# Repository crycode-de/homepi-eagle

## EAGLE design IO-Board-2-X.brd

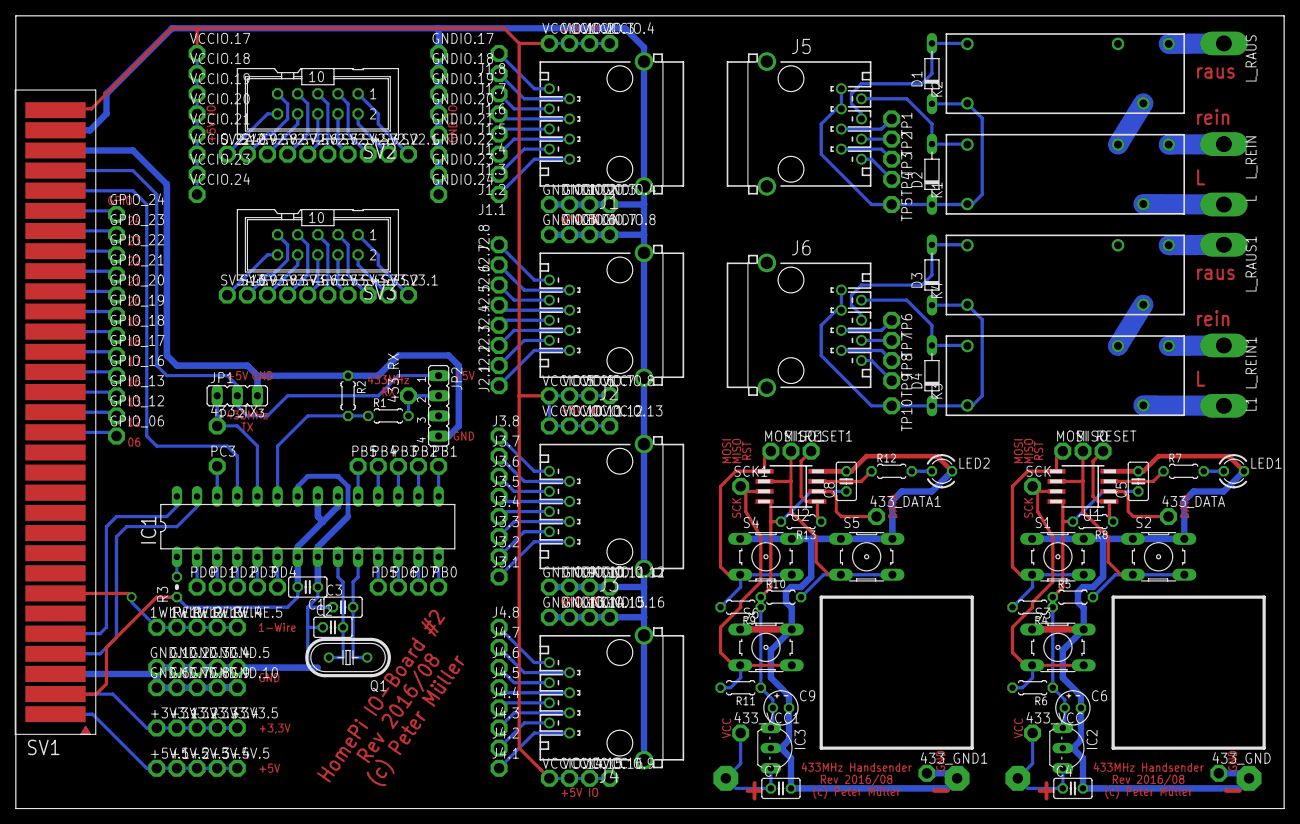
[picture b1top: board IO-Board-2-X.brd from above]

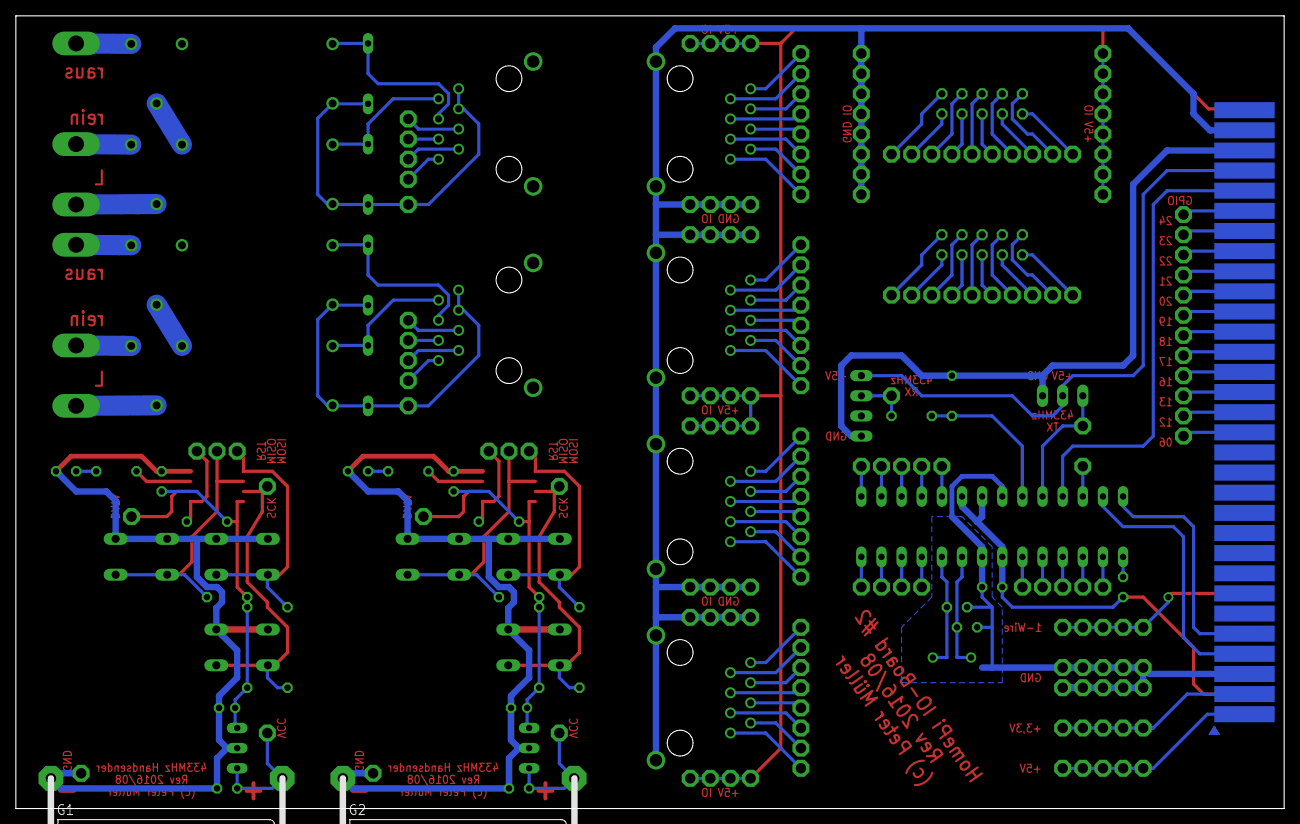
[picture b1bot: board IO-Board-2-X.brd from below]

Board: 2 copper layers, 160.0 x 100.0 mm, 241 parts (2 on the bottom side), 138 nets.

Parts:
1WIRE.1, 1WIRE.2, 1WIRE.3, 1WIRE.4, 1WIRE.5, 433_DATA, 433_DATA1, 433_GND, 433_GND1, 433_RX, 433_TX, 433_VCC, 433_VCC1: TPPAD1-13; P1-13
+3V3.1, +3V3.2, +3V3.3, +3V3.4, +3V3.5, +5V.1, +5V.2, +5V.3, +5V.4, +5V.5: TPPAD1-13; P1-13
C1, C4, C5, C7, C8: 100nF; C025-025X050
C2, C3: 22pF; C025-025X050
C6, C9: 10µF; E2-4
D1, D2, D3, D4: D-7.5
G1, G2: GP23A
GND.1, GND.2, GND.3, GND.4, GND.5, GND.6, GND.7, GND.8, GND.9, GND.10: TPPAD1-13; P1-13
GNDIO.1, GNDIO.2, GNDIO.3, GNDIO.4, GNDIO.5, GNDIO.6, GNDIO.7, GNDIO.8, GNDIO.9, GNDIO.10, GNDIO.11, GNDIO.12, GNDIO.13, GNDIO.14, GNDIO.15, GNDIO.16, GNDIO.17, GNDIO.18, GNDIO.19, GNDIO.20, GNDIO.21, GNDIO.22, GNDIO.23, GNDIO.24: TPPAD1-13; P1-13
GPIO_06, GPIO_12, GPIO_13, GPIO_16, GPIO_17, GPIO_18, GPIO_19, GPIO_20, GPIO_21, GPIO_22, GPIO_23, GPIO_24: TPPAD1-13; P1-13
IC1: MEGA8-P; DIL28-3
IC2, IC3: LM2936-5.0; TO92-INLINE
J1, J2, J3, J4, J5, J6: 555153-1
J1.1, J1.2, J1.3, J1.4, J1.5, J1.6, J1.7, J1.8, J2.1, J2.2, J2.3, J2.4, J2.5, J2.6, J2.7, J2.8, J3.1, J3.2, J3.3, J3.4, J3.5, J3.6, J3.7, J3.8, J4.1, J4.2, J4.3, J4.4, J4.5, J4.6, J4.7, J4.8: TPPAD1-13; P1-13
JP1: JP2
JP2: JP4
K1, K2, K3, K4: FINDER-43.41
L, L1: TPPAD1-20Y; P1-20Y
LED1, LED2: LED3MM
L_RAUS, L_RAUS1: TPPAD1-20Y; P1-20Y
L_REIN, L_REIN1: TPPAD1-20Y; P1-20Y
MISO, MISO1: TPPAD1-13; P1-13
MOSI, MOSI1: TPPAD1-13; P1-13
PB0, PB1, PB2, PB3, PB4, PB5: TPPAD1-13; P1-13
PC3: TPPAD1-13; P1-13
PD0, PD1, PD2, PD3, PD4, PD5, PD6, PD7: TPPAD1-13; P1-13
Q1: 8MHz; HC49U-V
R1, R4, R5, R6, R8, R9, R10, R11, R13: 10k; 0204/5
R2: 18k; 0204/5
R3: 10k; 0204V
R7, R12: 1k5; 0204/5
RESET, RESET1: TPPAD1-13; P1-13
S1, S2, S3, S4, S5, S6: B3F-10XX
SCK, SCK1: TPPAD1-13; P1-13
SV1: PLATINENVERBINDER-31SMD; PLATINENVERBINDER-31-SMD
SV2, SV3: ML10
SV2.1, SV2.2, SV2.3, SV2.4, SV2.5, SV2.6, SV2.7, SV2.8, SV2.9, SV2.10, SV3.1, SV3.2, SV3.3, SV3.4, SV3.5, SV3.6, SV3.7, SV3.8, SV3.9, SV3.10: TPPAD1-13; P1-13
TP1, TP2, TP3, TP4, TP5, TP6, TP7, TP8, TP9, TP10: TPPAD1-13; P1-13
U1, U2: ATTINY85V-10S; SOIC8_EIAJ_208MIL
VCCIO.1, VCCIO.2, VCCIO.3, VCCIO.4, VCCIO.5, VCCIO.6, VCCIO.7, VCCIO.8, VCCIO.9, VCCIO.10, VCCIO.11, VCCIO.12, VCCIO.13, VCCIO.14, VCCIO.15, VCCIO.16, VCCIO.17, VCCIO.18, VCCIO.19, VCCIO.20, VCCIO.21, VCCIO.22, VCCIO.23, VCCIO.24: TPPAD1-13; P1-13

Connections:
1WIRE: 1WIRE.1.TP, 1WIRE.2.TP, 1WIRE.3.TP, 1WIRE.4.TP, 1WIRE.5.TP, SV1.7, SV1.7T
433MHZ_INT: IC1.25, SV1.27, SV1.27T
433MHZ_RX: 433_RX.TP, JP2.2, R1.2
433MHZ_TX: 433_TX.TP, IC1.24, JP1.1
+3V3: +3V3.1.TP, +3V3.2.TP, +3V3.3.TP, +3V3.4.TP, +3V3.5.TP, C1.2, IC1.7, IC1.20, IC1.21, R3.1, SV1.2, SV1.2T
+5V: +5V.1.TP, +5V.2.TP, +5V.3.TP, +5V.4.TP, +5V.5.TP, SV1.1, SV1.1T
+5V1: C5.1, C6.+, IC2.VO, R4.1, R5.1, R6.1, R8.2, U1.8
+5V2: C8.1, C9.+, IC3.VO, R9.1, R10.1, R11.1, R13.2, U2.8
+5V_2: JP1.2, JP2.1, SV1.28, SV1.28T
+12V: 433_VCC.TP, C4.1, G1.+, IC2.VIN
+12V1: 433_VCC1.TP, C7.1, G2.+, IC3.VIN
GND: C1.1, C2.1, C3.1, GND.1.TP, GND.2.TP, GND.3.TP, GND.4.TP, GND.5.TP, GND.6.TP, GND.7.TP, GND.8.TP, GND.9.TP, GND.10.TP, IC1.8, IC1.22, SV1.3, SV1.3T
GND1: 433_GND.TP, C4.2, C5.2, C6.-, G1.-, IC2.GND, LED1.K, S1.1, S1.2, S2.1, S2.2, S3.1, S3.2, U1.4
GND2: 433_GND1.TP, C7.2, C8.2, C9.-, G2.-, IC3.GND, LED2.K, S4.1, S4.2, S5.1, S5.2, S6.1, S6.2, U2.4
GNDIO: GNDIO.1.TP, GNDIO.2.TP, GNDIO.3.TP, GNDIO.4.TP, GNDIO.5.TP, GNDIO.6.TP, GNDIO.7.TP, GNDIO.8.TP, GNDIO.9.TP, GNDIO.10.TP, GNDIO.11.TP, GNDIO.12.TP, GNDIO.13.TP, GNDIO.14.TP, GNDIO.15.TP, GNDIO.16.TP, GNDIO.17.TP, GNDIO.18.TP, GNDIO.19.TP, GNDIO.20.TP, GNDIO.21.TP, GNDIO.22.TP, GNDIO.23.TP, GNDIO.24.TP, J1.G1, J1.G2, J2.G1, J2.G2, J3.G1, J3.G2, J4.G1, J4.G2, SV1.30, SV1.30T
GND_2: JP1.3, JP2.4, R2.1, SV1.29, SV1.29T
MARKISE_RAUS: D1.A, J5.4, K2.A2
MARKISE_RAUS1: D3.A, J6.4, K4.A2
MARKISE_REIN: D2.A, J5.2, K1.A2
MARKISE_REIN1: D4.A, J6.2, K3.A2
unnamed: J4.4, J4.4.TP
unnamed: IC1.23, R1.1, R2.2
unnamed: J4.3, J4.3.TP
unnamed: J4.2, J4.2.TP
unnamed: J4.1, J4.1.TP
unnamed: IC1.1, R3.2
unnamed: GPIO_24.TP, SV1.26, SV1.26T
unnamed: IC1.26, PC3.TP
unnamed: IC1.2, PD0.TP
unnamed: IC1.3, PD1.TP
unnamed: IC1.4, PD2.TP
unnamed: IC1.5, PD3.TP
unnamed: IC1.6, PD4.TP
unnamed: IC1.11, PD5.TP
unnamed: IC1.12, PD6.TP
unnamed: IC1.13, PD7.TP
unnamed: IC1.14, PB0.TP
unnamed: IC1.15, PB1.TP
unnamed: IC1.16, PB2.TP
unnamed: IC1.17, PB3.TP
unnamed: IC1.18, PB4.TP
unnamed: IC1.19, PB5.TP
unnamed: C3.2, IC1.10, Q1.1
unnamed: C2.2, IC1.9, Q1.2
unnamed: MOSI.TP, R4.2, S1.3, S1.4, U1.5
unnamed: MISO.TP, R5.2, S2.3, S2.4, U1.6
unnamed: R6.2, S3.3, S3.4, SCK.TP, U1.7
unnamed: R7.1, U1.3
unnamed: LED1.A, R7.2
unnamed: 433_DATA.TP, U1.2
unnamed: R8.1, RESET.TP, U1.1
unnamed: MOSI1.TP, R9.2, S4.3, S4.4, U2.5
unnamed: MISO1.TP, R10.2, S5.3, S5.4, U2.6
unnamed: R11.2, S6.3, S6.4, SCK1.TP, U2.7
unnamed: R12.1, U2.3
unnamed: J1.1, J1.1.TP
unnamed: J1.2, J1.2.TP
unnamed: J1.3, J1.3.TP
unnamed: J1.4, J1.4.TP
unnamed: J1.5, J1.5.TP
unnamed: J1.6, J1.6.TP
unnamed: J1.7, J1.7.TP
unnamed: J1.8, J1.8.TP
unnamed: J2.1, J2.1.TP
unnamed: J2.2, J2.2.TP
unnamed: J2.3, J2.3.TP
unnamed: J2.4, J2.4.TP
unnamed: J2.5, J2.5.TP
unnamed: J2.6, J2.6.TP
unnamed: J2.7, J2.7.TP
unnamed: J2.8, J2.8.TP
unnamed: LED2.A, R12.2
unnamed: 433_DATA1.TP, U2.2
unnamed: R13.1, RESET1.TP, U2.1
unnamed: K1.12, K2.11
unnamed: K1.11, L.TP
unnamed: K1.14, L_REIN.TP
unnamed: K2.14, L_RAUS.TP
unnamed: J5.5, TP1.TP
unnamed: J5.6, TP2.TP
unnamed: J5.7, TP3.TP
unnamed: J5.8, TP4.TP
unnamed: K3.12, K4.11
unnamed: K3.11, L1.TP
unnamed: K3.14, L_REIN1.TP
unnamed: K4.14, L_RAUS1.TP
unnamed: J6.5, TP6.TP
unnamed: J6.6, TP7.TP
unnamed: J6.7, TP8.TP
unnamed: J6.8, TP9.TP
unnamed: J3.1, J3.1.TP
unnamed: J3.2, J3.2.TP
unnamed: J3.3, J3.3.TP
unnamed: J3.4, J3.4.TP
unnamed: J3.5, J3.5.TP
unnamed: J3.6, J3.6.TP
unnamed: J3.7, J3.7.TP
unnamed: J3.8, J3.8.TP
unnamed: J4.5, J4.5.TP
unnamed: J4.6, J4.6.TP
unnamed: J4.7, J4.7.TP
unnamed: J4.8, J4.8.TP
unnamed: GPIO_23.TP, SV1.25, SV1.25T
unnamed: GPIO_22.TP, SV1.24, SV1.24T
unnamed: GPIO_21.TP, SV1.23, SV1.23T
unnamed: GPIO_20.TP, SV1.22, SV1.22T
unnamed: GPIO_19.TP, SV1.21, SV1.21T
unnamed: GPIO_18.TP, SV1.20, SV1.20T
unnamed: GPIO_17.TP, SV1.19, SV1.19T
unnamed: GPIO_16.TP, SV1.18, SV1.18T
unnamed: GPIO_13.TP, SV1.17, SV1.17T
unnamed: GPIO_12.TP, SV1.16, SV1.16T
unnamed: GPIO_06.TP, SV1.15, SV1.15T
unnamed: SV2.1, SV2.1.TP
unnamed: SV2.2, SV2.2.TP
unnamed: SV2.3, SV2.3.TP
unnamed: SV2.4, SV2.4.TP
unnamed: SV2.5, SV2.5.TP
unnamed: SV2.6, SV2.6.TP
unnamed: SV2.7, SV2.7.TP
unnamed: SV2.8, SV2.8.TP
unnamed: SV2.9, SV2.9.TP
unnamed: SV2.10, SV2.10.TP
unnamed: SV3.1, SV3.1.TP
unnamed: SV3.2, SV3.2.TP
unnamed: SV3.3, SV3.3.TP
unnamed: SV3.4, SV3.4.TP
unnamed: SV3.5, SV3.5.TP
unnamed: SV3.6, SV3.6.TP
unnamed: SV3.7, SV3.7.TP
unnamed: SV3.8, SV3.8.TP
unnamed: SV3.9, SV3.9.TP
unnamed: SV3.10, SV3.10.TP
SCL: IC1.28, SV1.5, SV1.5T
SDA: IC1.27, SV1.4, SV1.4T
VCCIO: SV1.31, SV1.31T, VCCIO.1.TP, VCCIO.2.TP, VCCIO.3.TP, VCCIO.4.TP, VCCIO.5.TP, VCCIO.6.TP, VCCIO.7.TP, VCCIO.8.TP, VCCIO.9.TP, VCCIO.10.TP, VCCIO.11.TP, VCCIO.12.TP, VCCIO.13.TP, VCCIO.14.TP, VCCIO.15.TP, VCCIO.16.TP, VCCIO.17.TP, VCCIO.18.TP, VCCIO.19.TP, VCCIO.20.TP, VCCIO.21.TP, VCCIO.22.TP, VCCIO.23.TP, VCCIO.24.TP
VCCIO1: D1.C, D2.C, J5.1, J5.3, K1.A1, K2.A1, TP5.TP
VCCIO2: D3.C, D4.C, J6.1, J6.3, K3.A1, K4.A1, TP10.TP

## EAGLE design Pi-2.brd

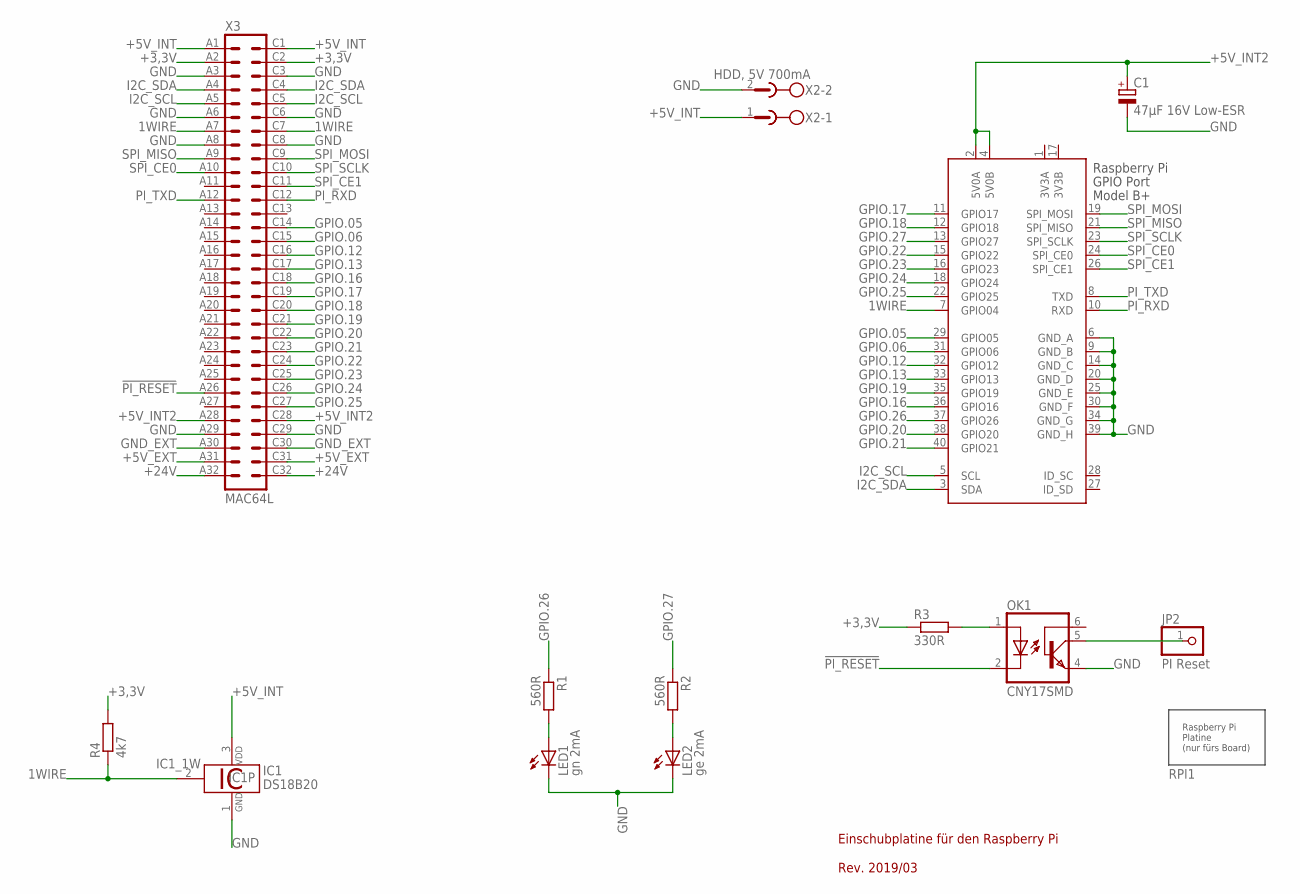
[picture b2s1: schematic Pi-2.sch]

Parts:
C1: 47µF 16V Low-ESR; E2-5
IC1: DS18B20; TO92-
JP2: PI Reset; 1X01
LED1: gn 2mA; LED3MM
LED2: ge 2mA; LED3MM
OK1: CNY17SMD; DIL06_SMD
R1, R2: 560R; R1206
R3: 330R; R1206
R4: 4k7; R1206
RPI1: RASPBERRYPI-PLATINE
X1: RASPI_GPIO_B+#_PIN; RASPI_GPIO_B+_PIN
X2: HDD, 5V 700mA; MSTBA2
X3: MAC64L

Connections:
1WIRE: IC1.2 (1W), R4.1, X1.7 (GPIO04), X3.A7, X3.C7
3V3A: X1.1 (3V3A)
3V3B: X1.17 (3V3B)
!PI_RESET: OK1.2 (C), X3.A26
+3,3V: R3.1, R4.2, X3.A2, X3.C2
+5V_EXT: X3.A31, X3.C31
+5V_INT: IC1.3 (VDD), X2.1, X3.A1, X3.C1
+5V_INT2: C1.+, X1.2 (5V0A), X1.4 (5V0B), X3.A28, X3.C28
+24V: X3.A32, X3.C32
GND: C1.-, IC1.1 (GND), LED1.K (C), LED2.K (C), OK1.4 (EMI), X1.6 (GND_A), X1.9 (GND_B), X1.14 (GND_C), X1.20 (GND_D), X1.25 (GND_E), X1.30 (GND_F), X1.34 (GND_G), X1.39 (GND_H), X2.2, X3.A3, X3.A6, X3.A8, X3.A29, X3.C3, X3.C6, X3.C8, X3.C29
GND_EXT: X3.A30, X3.C30
GPIO.05: X1.29 (GPIO05), X3.C14
GPIO.06: X1.31 (GPIO06), X3.C15
GPIO.12: X1.32 (GPIO12), X3.C16
GPIO.13: X1.33 (GPIO13), X3.C17
GPIO.16: X1.36 (GPIO16), X3.C18
GPIO.17: X1.11 (GPIO17), X3.C19
GPIO.18: X1.12 (GPIO18), X3.C20
GPIO.19: X1.35 (GPIO19), X3.C21
GPIO.20: X1.38 (GPIO20), X3.C22
GPIO.21: X1.40 (GPIO21), X3.C23
GPIO.22: X1.15 (GPIO22), X3.C24
GPIO.23: X1.16 (GPIO23), X3.C25
GPIO.24: X1.18 (GPIO24), X3.C26
GPIO.25: X1.22 (GPIO25), X3.C27
GPIO.26: R1.1, X1.37 (GPIO26)
GPIO.27: R2.1, X1.13 (GPIO27)
I2C_SCL: X1.5 (SCL), X3.A5, X3.C5
I2C_SDA: X1.3 (SDA), X3.A4, X3.C4
unnamed: LED2.A, R2.2
unnamed: OK1.1 (A), R3.2
unnamed: JP2.1, OK1.5 (COL)
unnamed: LED1.A, R1.2
PI_RXD: X1.10 (RXD), X3.C12
PI_TXD: X1.8 (TXD), X3.A12
SPI_CE0: X1.24 (SPI_CE0), X3.A10
SPI_CE1: X1.26 (SPI_CE1), X3.C11
SPI_MISO: X1.21 (SPI_MISO), X3.A9
SPI_MOSI: X1.19 (SPI_MOSI), X3.C9
SPI_SCLK: X1.23 (SPI_SCLK), X3.C10

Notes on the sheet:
Einschubplatine für den Raspberry Pi Rev. 2019/03

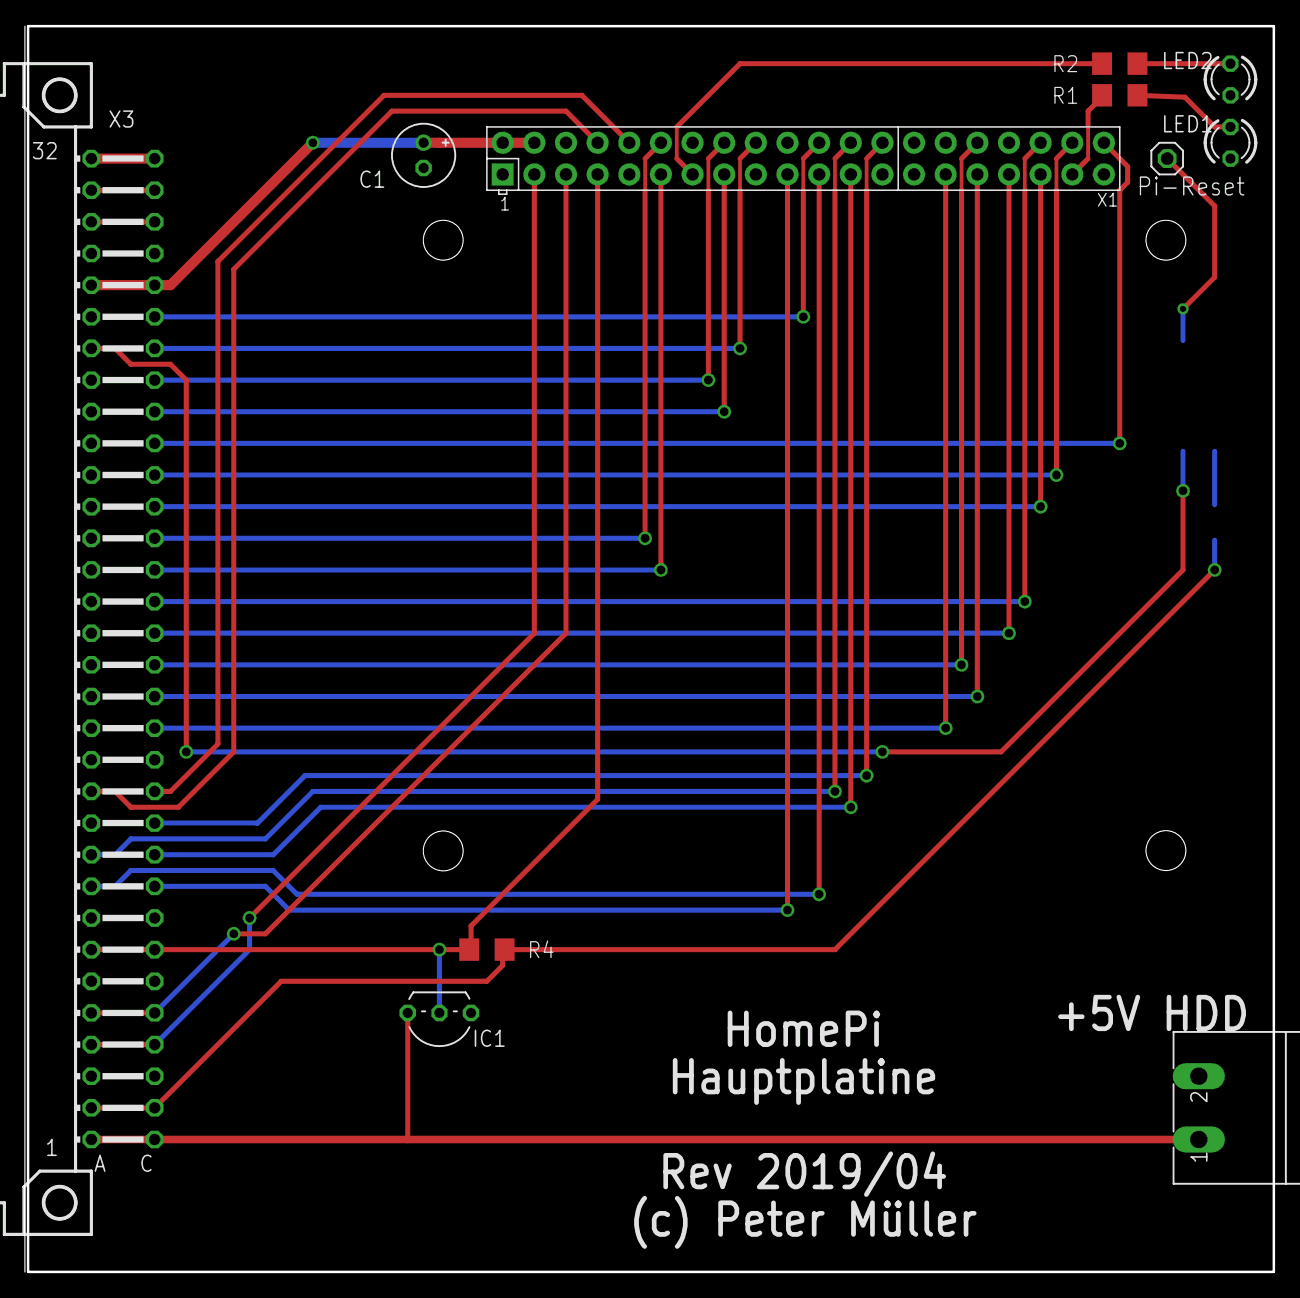
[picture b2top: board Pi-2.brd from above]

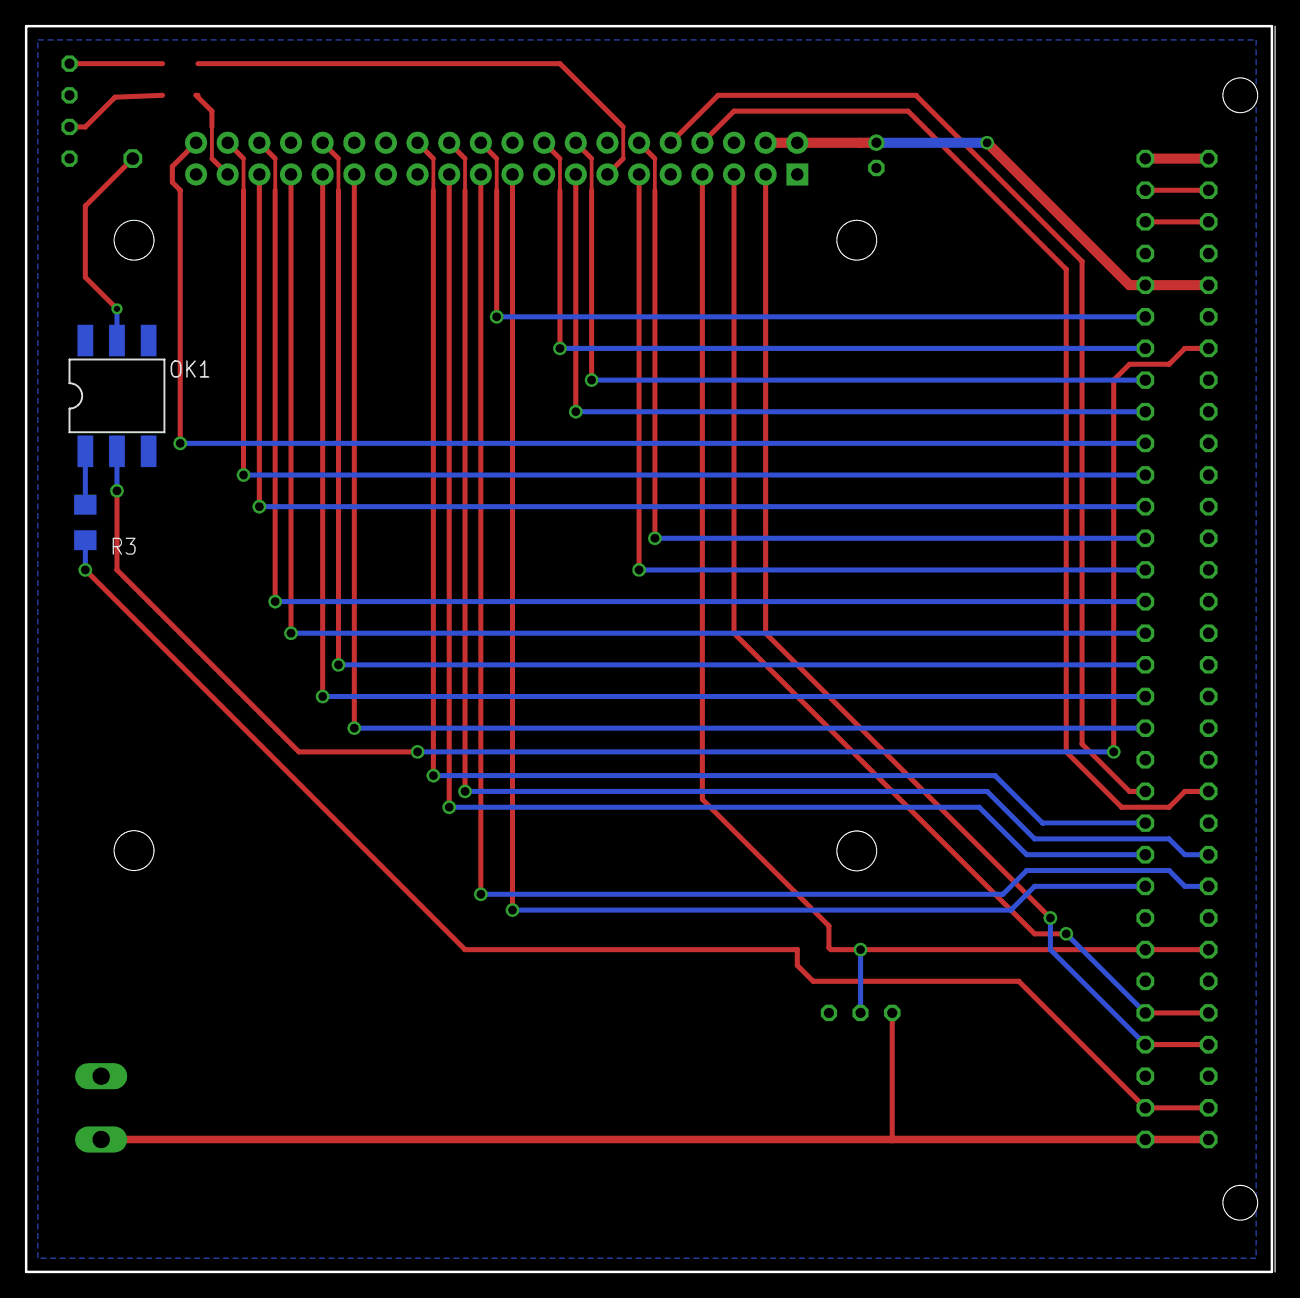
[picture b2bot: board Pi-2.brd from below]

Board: 2 copper layers, 100.0 x 100.0 mm, 14 parts (2 on the bottom side), 38 nets.

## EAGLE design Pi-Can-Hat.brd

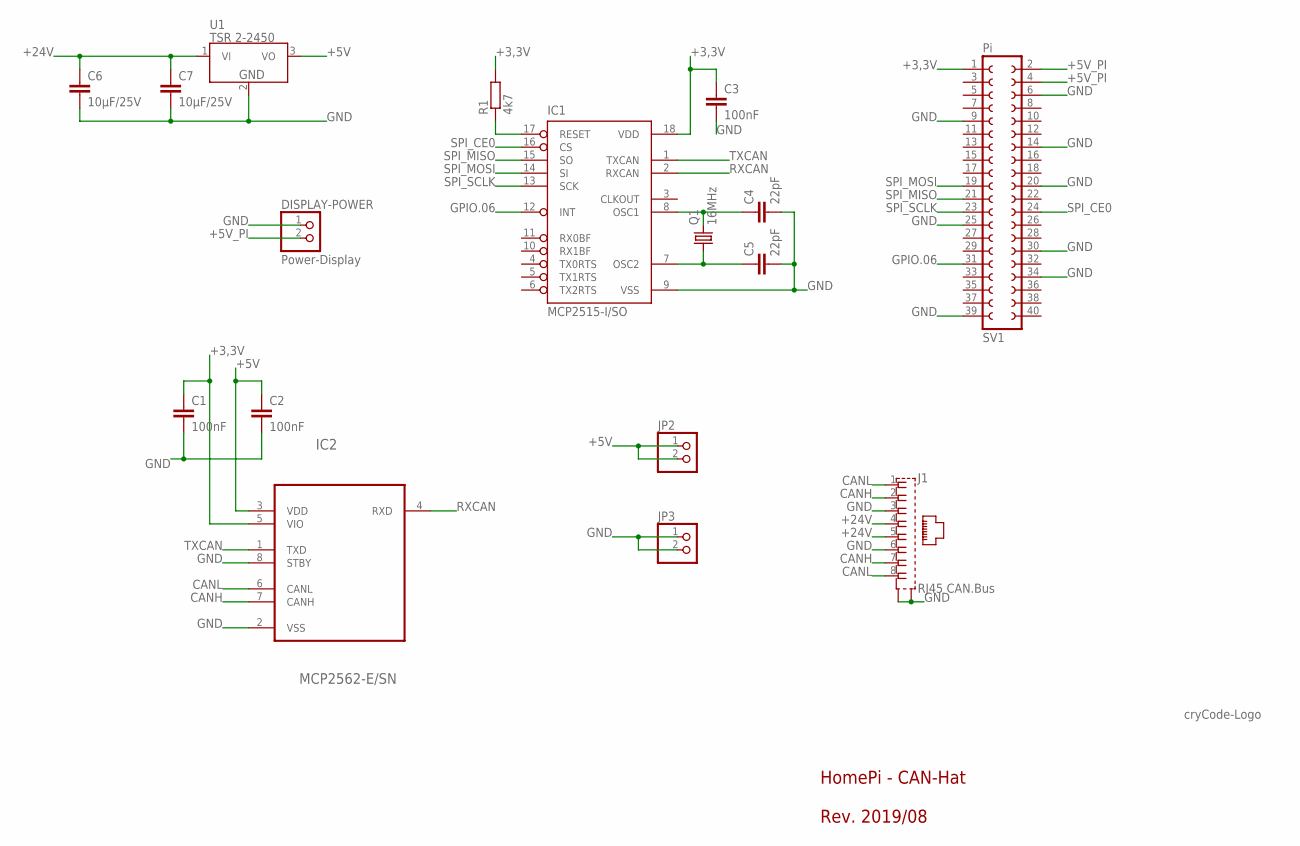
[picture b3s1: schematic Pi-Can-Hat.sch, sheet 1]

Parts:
C1, C2, C3: 100nF; C1206
C4, C5: 22pF; C1206
C6, C7: 10µF/25V; C1206
DISPLAY-POWER: Power-Display; 1X02/90
IC1: MCP2515-I/SO; SO18L
IC2: MCP2562-E/SN; SO08
J1: RJ45 CAN.Bus; MEBP_8-8G
JP2, JP3: PINHD-1X2; 1X02
Q1: 16MHz; HC49UP
R1: 4k7; R1206
SV1: Pi; FE20-2
U1: TSR 2-2450; TSR2
U$1: LOGO30MM; 30MM

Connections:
+3,3V: C1.1, C3.1, IC1.18 (VDD), IC2.5 (VIO), R1.2, SV1.1
+5V: C2.1, IC2.3 (VDD), JP2.1, JP2.2, U1.3 (VO); also elsewhere on the board
+5V_PI: DISPLAY-POWER.2, SV1.2, SV1.4; also elsewhere on the board
+24V: C6.1, C7.1, J1.4, J1.5, U1.1 (VI)
CANH: IC2.7 (CANH), J1.2, J1.7; also elsewhere on the board
CANL: IC2.6 (CANL), J1.1, J1.8; also elsewhere on the board
GND: C1.2, C2.2, C3.2, C4.2, C5.2, C6.2, C7.2, DISPLAY-POWER.1, IC1.9 (VSS), IC2.2 (VSS), IC2.8 (STBY), J1.3, J1.6, J1.G1 (S1), J1.G2 (S2), JP3.1, JP3.2, SV1.6, SV1.9, SV1.14, SV1.20, SV1.25, SV1.30, SV1.34, SV1.39, U1.2 (GND); also elsewhere on the board
GPIO.06: IC1.12 (INT), SV1.31
unnamed: C4.1, IC1.8 (OSC1), Q1.2
unnamed: IC1.17 (RESET), R1.1
unnamed: C5.1, IC1.7 (OSC2), Q1.1
RXCAN: IC1.2 (RXCAN), IC2.4 (RXD)
SPI_CE0: IC1.16 (CS), SV1.24
SPI_MISO: IC1.15 (SO), SV1.21
SPI_MOSI: IC1.14 (SI), SV1.19
SPI_SCLK: IC1.13 (SCK), SV1.23
TXCAN: IC1.1 (TXCAN), IC2.1 (TXD)

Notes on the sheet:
HomePi - CAN-Hat Rev. 2019/08

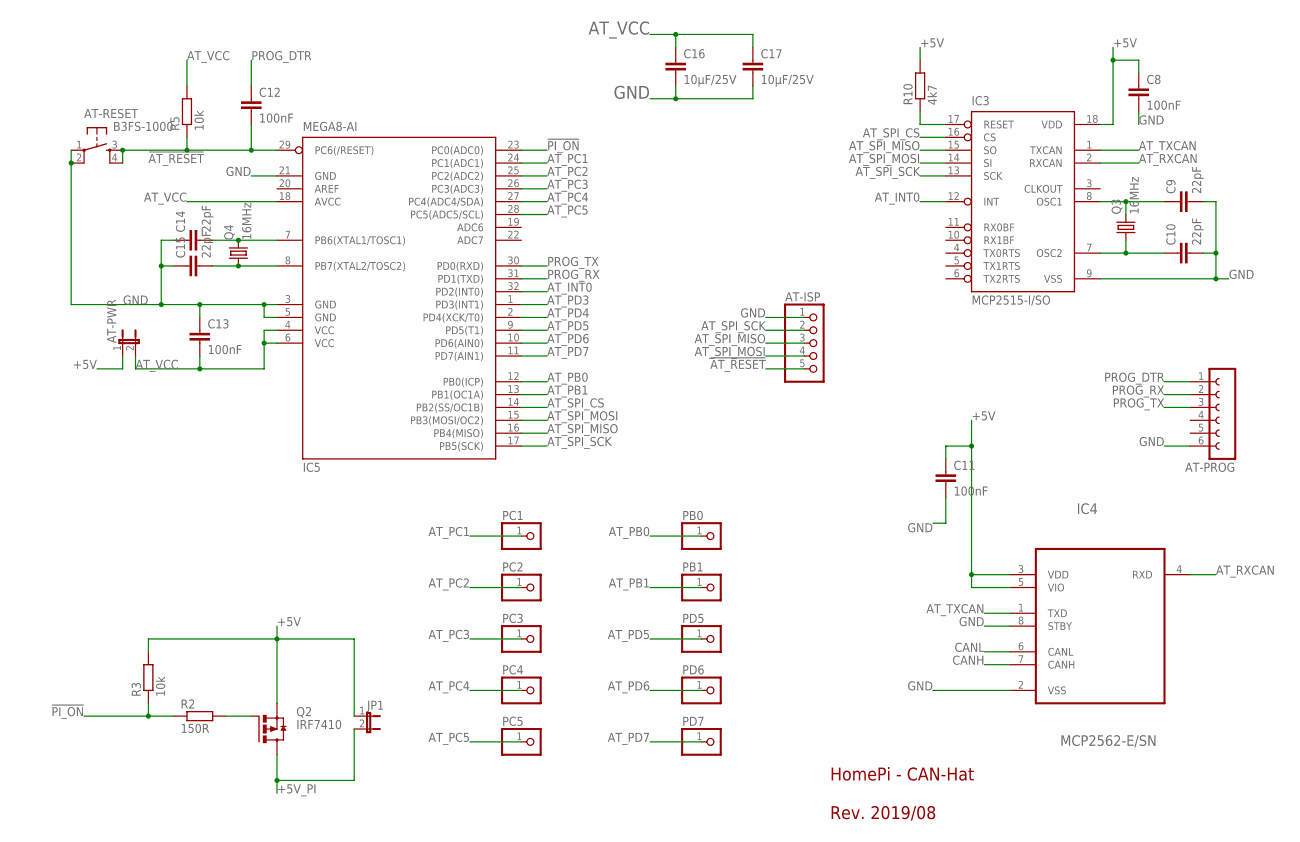
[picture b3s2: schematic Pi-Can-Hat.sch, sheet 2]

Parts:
AT-ISP: PINHD-1X5; 1X05
AT-PROG: FE06W
AT-PWR: JP1E; JP1
AT-RESET: B3FS-1000
C8, C11, C12, C13: 100nF; C1206
C9, C10, C14, C15: 22pF; C1206
C16, C17: 10µF/25V; C1206
IC3: MCP2515-I/SO; SO18L
IC4: MCP2562-E/SN; SO08
IC5: MEGA8-AI; TQFP32-08
JP1: JP1E; JP1
PB0, PB1: PINHD-1X1; 1X01
PC1, PC2, PC3, PC4, PC5: PINHD-1X1; 1X01
PD5, PD6, PD7: PINHD-1X1; 1X01
Q2: IRF7410; SO08
Q3, Q4: 16MHz; HC49UP
R2: 150R; R1206
R3, R5: 10k; R1206
R10: 4k7; R1206

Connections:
!AT_RESET: AT-ISP.5, AT-RESET.3 (S), AT-RESET.4 (S1), C12.2, IC5.29 (PC6(/RESET)), R5.1
!PI_ON: IC5.23 (PC0(ADC0)), R2.1, R3.1
+5V: AT-PWR.1, C8.1, C11.1, IC3.18 (VDD), IC4.3 (VDD), IC4.5 (VIO), JP1.1, Q2.1 (S), Q2.2 (S), Q2.3 (S), R3.2, R10.2; also elsewhere on the board
+5V_PI: JP1.2, Q2.5 (D), Q2.6 (D), Q2.7 (D), Q2.8 (D); also elsewhere on the board
AT_INT0: IC3.12 (INT), IC5.32 (PD2(INT0))
AT_PB0: IC5.12 (PB0(ICP)), PB0.1
AT_PB1: IC5.13 (PB1(OC1A)), PB1.1
AT_PC1: IC5.24 (PC1(ADC1)), PC1.1
AT_PC2: IC5.25 (PC2(ADC2)), PC2.1
AT_PC3: IC5.26 (PC3(ADC3)), PC3.1
AT_PC4: IC5.27 (PC4(ADC4/SDA)), PC4.1
AT_PC5: IC5.28 (PC5(ADC5/SCL)), PC5.1
AT_PD3: IC5.1 (PD3(INT1))
AT_PD4: IC5.2 (PD4(XCK/T0))
AT_PD5: IC5.9 (PD5(T1)), PD5.1
AT_PD6: IC5.10 (PD6(AIN0)), PD6.1
AT_PD7: IC5.11 (PD7(AIN1)), PD7.1
AT_RXCAN: IC3.2 (RXCAN), IC4.4 (RXD)
AT_SPI_CS: IC3.16 (CS), IC5.14 (PB2(SS/OC1B))
AT_SPI_MISO: AT-ISP.3, IC3.15 (SO), IC5.16 (PB4(MISO))
AT_SPI_MOSI: AT-ISP.4, IC3.14 (SI), IC5.15 (PB3(MOSI/OC2))
AT_SPI_SCK: AT-ISP.2, IC3.13 (SCK), IC5.17 (PB5(SCK))
AT_TXCAN: IC3.1 (TXCAN), IC4.1 (TXD)
AT_VCC: AT-PWR.2, C13.2, C16.1, C17.1, IC5.4 (VCC), IC5.6 (VCC), IC5.18 (AVCC), R5.2
CANH: IC4.7 (CANH); also elsewhere on the board
CANL: IC4.6 (CANL); also elsewhere on the board
GND: AT-ISP.1, AT-PROG.6, AT-RESET.1, AT-RESET.2 (P1), C8.2, C9.2, C10.2, C11.2, C13.1, C14.1, C15.1, C16.2, C17.2, IC3.9 (VSS), IC4.2 (VSS), IC4.8 (STBY), IC5.3 (GND), IC5.5 (GND), IC5.21 (GND); also elsewhere on the board
unnamed: Q2.4 (G), R2.2
unnamed: IC3.17 (RESET), R10.1
unnamed: C9.1, IC3.8 (OSC1), Q3.2
unnamed: C10.1, IC3.7 (OSC2), Q3.1
unnamed: C14.2, IC5.7 (PB6(XTAL1/TOSC1)), Q4.2
unnamed: C15.2, IC5.8 (PB7(XTAL2/TOSC2)), Q4.1
PROG_DTR: AT-PROG.1, C12.1
PROG_RX: AT-PROG.2, IC5.31 (PD1(TXD))
PROG_TX: AT-PROG.3, IC5.30 (PD0(RXD))

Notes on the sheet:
HomePi - CAN-Hat Rev. 2019/08

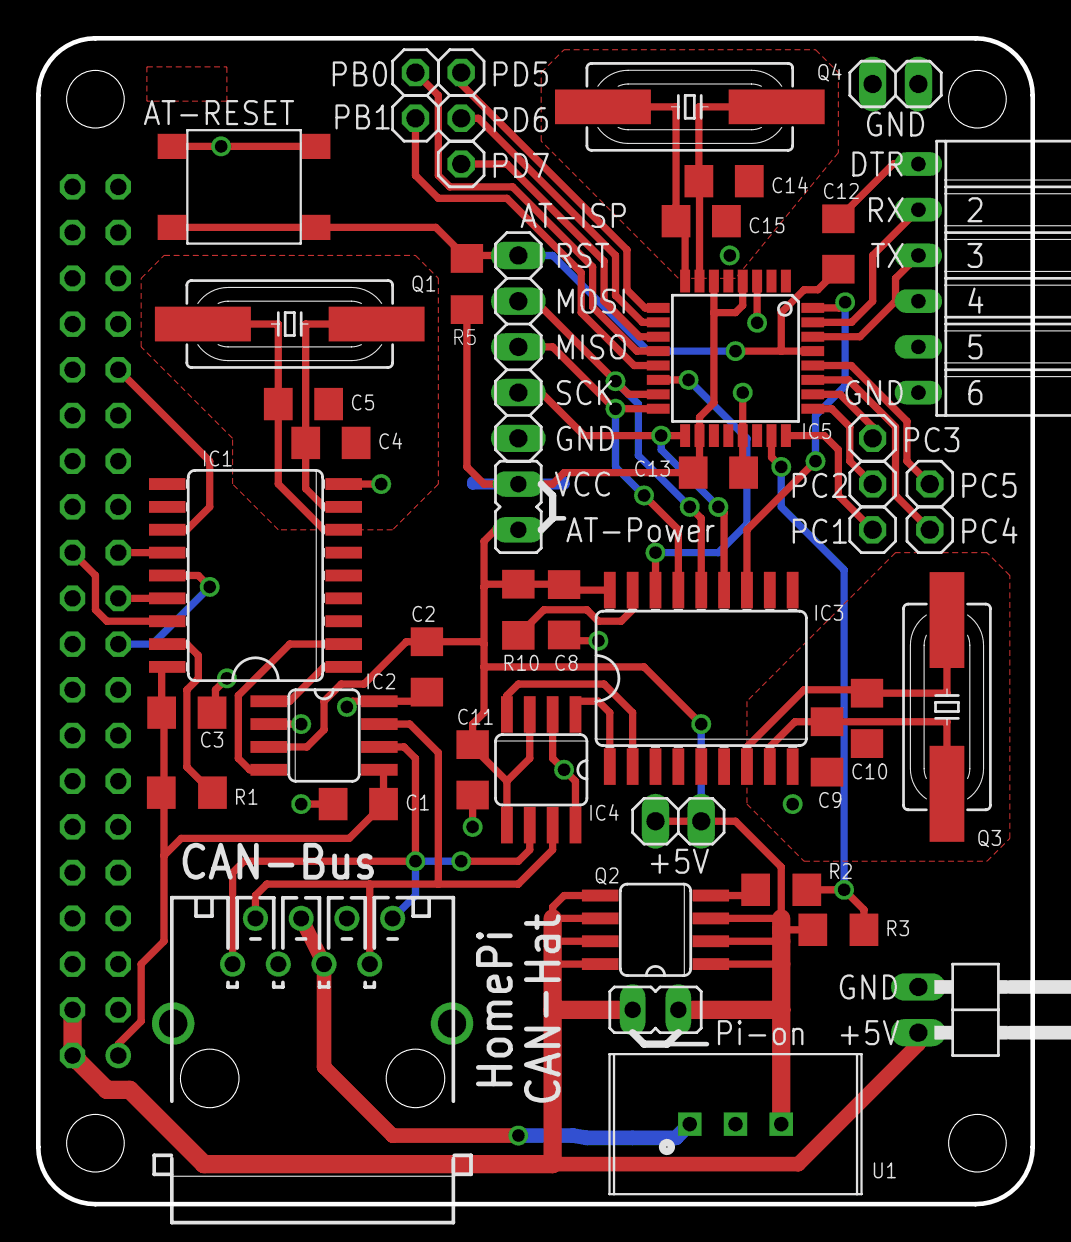
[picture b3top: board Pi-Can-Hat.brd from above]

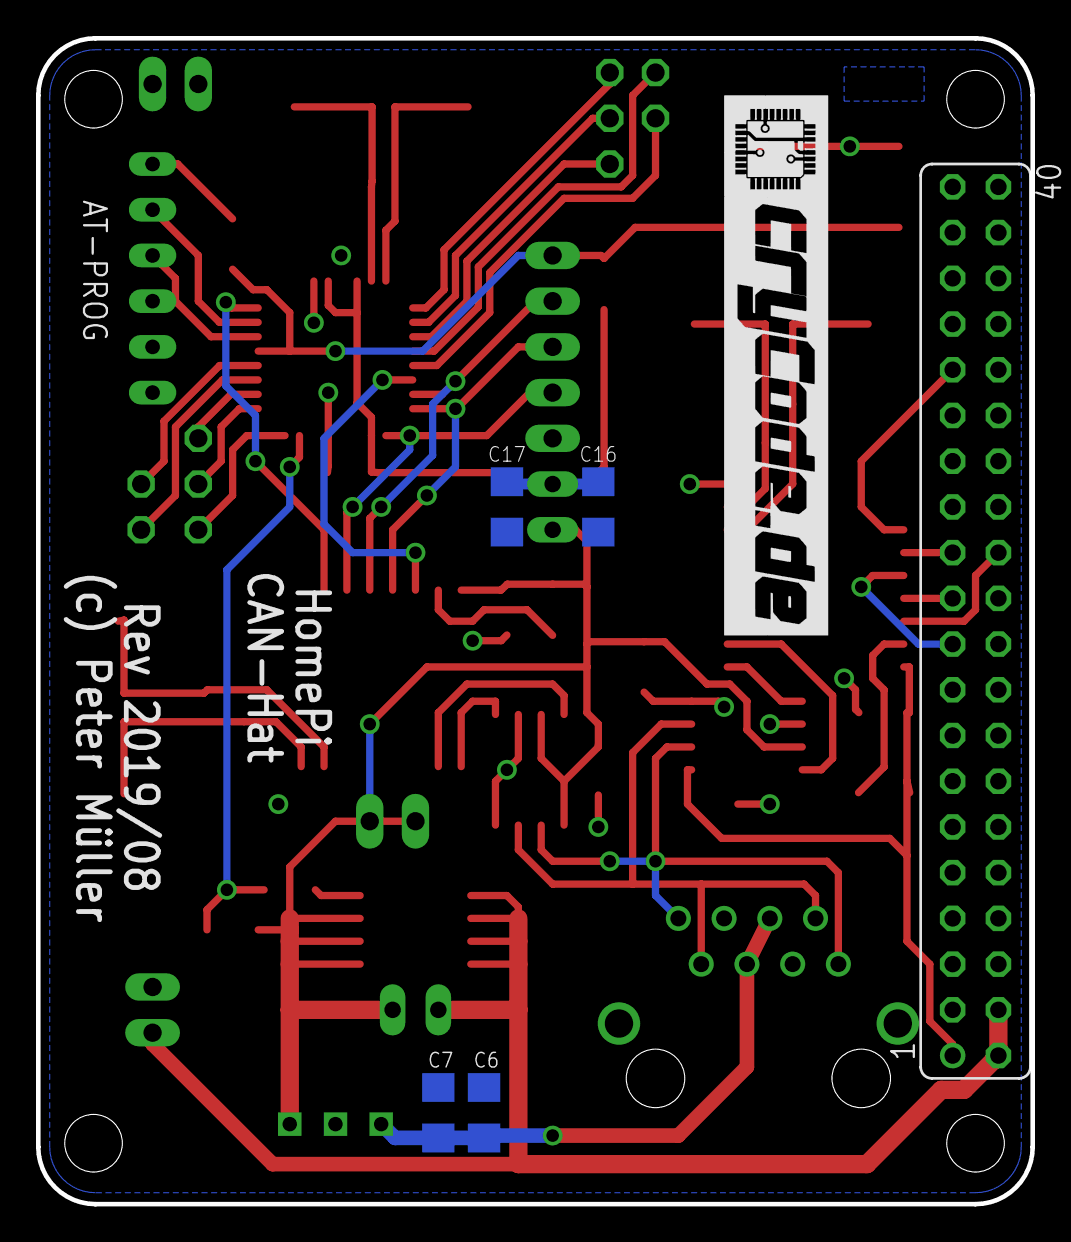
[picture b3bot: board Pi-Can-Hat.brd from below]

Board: 2 copper layers, 55.2 x 64.8 mm, 53 parts (6 on the bottom side), 46 nets.
